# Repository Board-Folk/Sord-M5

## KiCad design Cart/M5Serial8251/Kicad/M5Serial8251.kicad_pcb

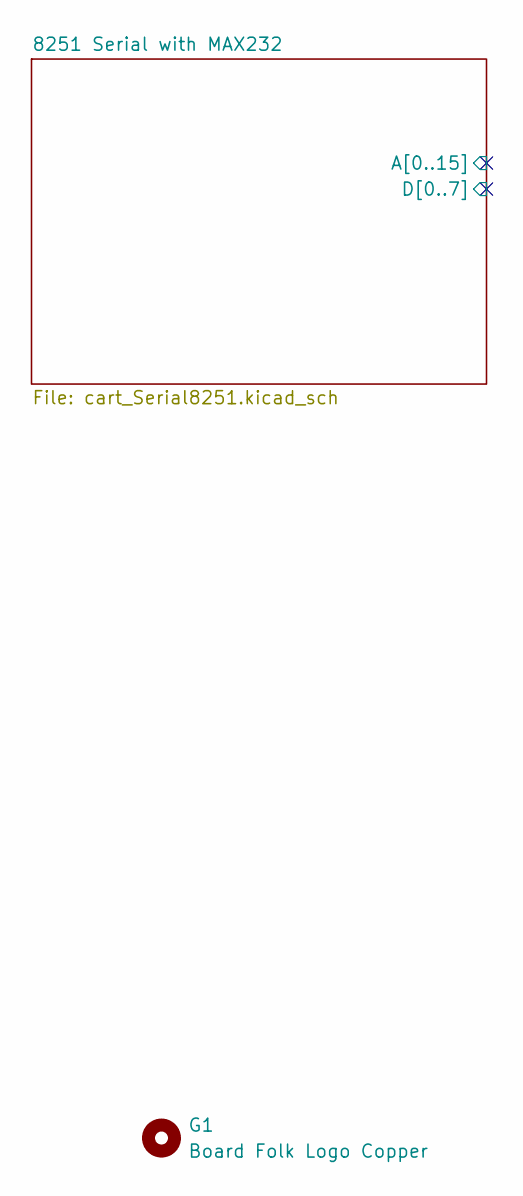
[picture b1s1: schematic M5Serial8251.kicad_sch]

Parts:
G1: Board Folk Logo Copper; BF8_copper

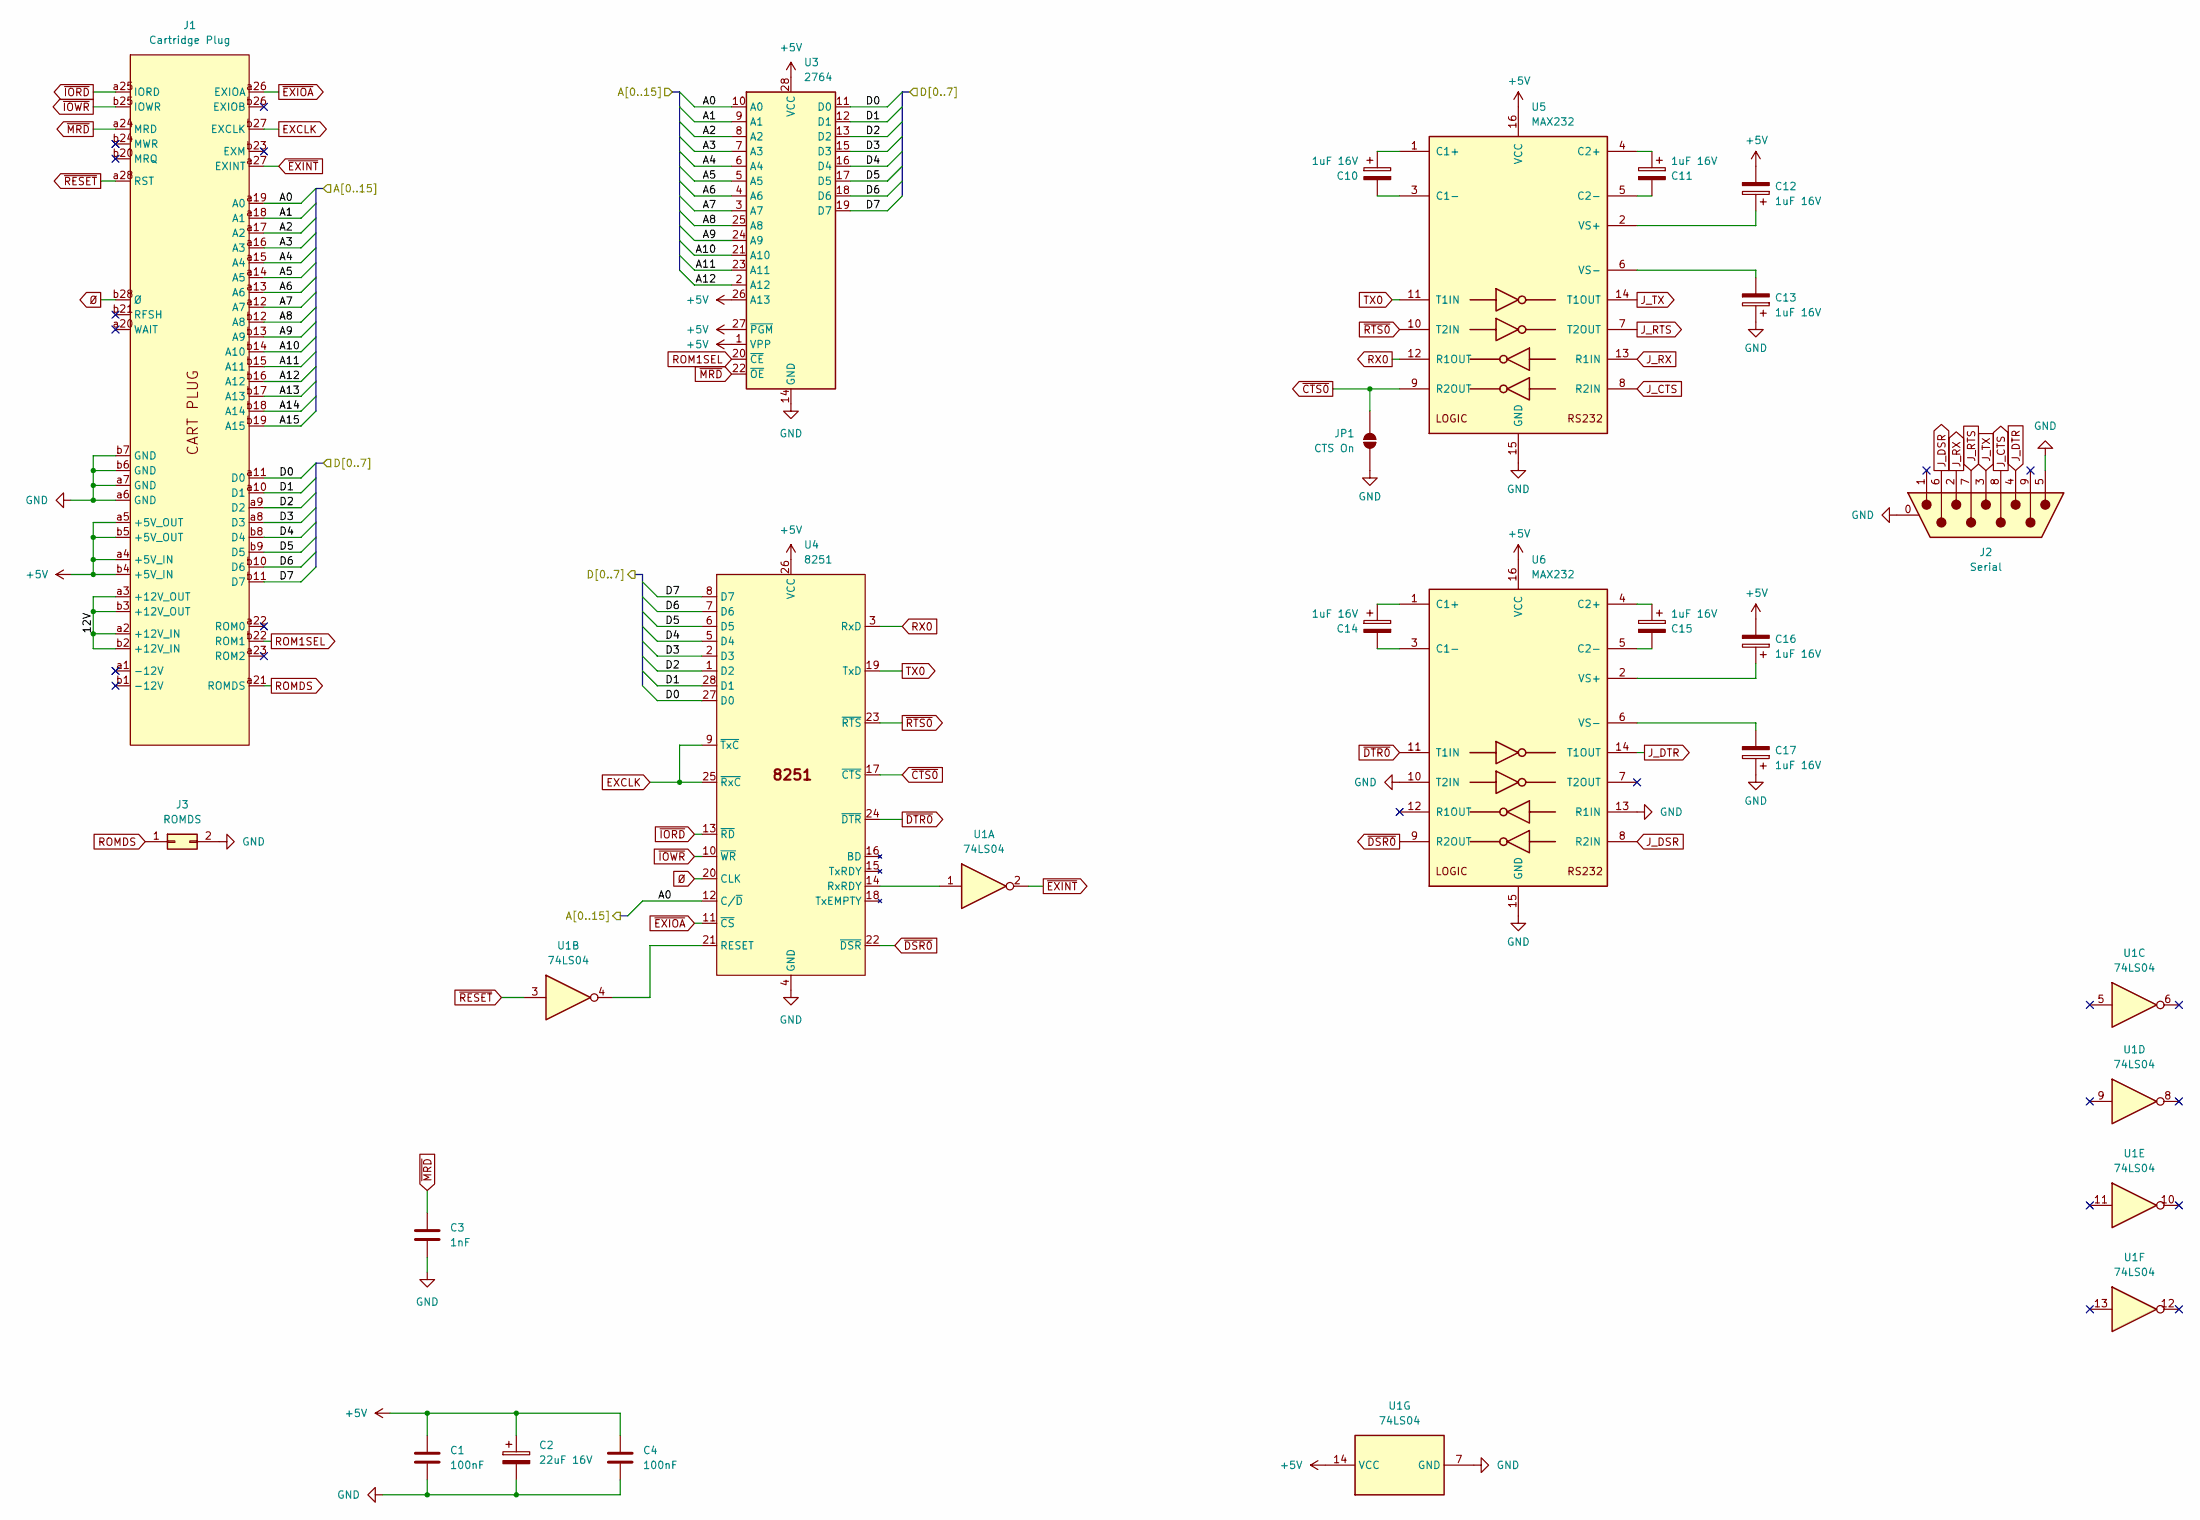
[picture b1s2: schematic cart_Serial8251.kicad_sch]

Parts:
C1, C4: 100nF; Ceramic_5mm
C2: 22uF 16V; CP_Axial_P15.00mm
C3: 1nF; Ceramic_5mm
C10, C11, C12, C13, C14, C15, C16, C17: 1uF 16V; Elect_2.54mm
J1: Cartridge Plug; Cart Edge
J2: Serial; SERIAL9
J3: ROMDS; ROM DS Select
JP1: CTS On; SolderJumper-2_P1.3mm_Open_RoundedPad1.0x1.5mm
U1: 74LS04; DIP-14_W7.62mm
U3: 2764; DIP-28_W15.24mm
U4: 8251; DIP-28_W15.24mm
U5, U6: MAX232; DIP-16_W7.62mm

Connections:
+5V: C1.1, C2.1, C4.1, C12.2, C16.2, J1.a4 (+5V_IN), J1.a5 (+5V_OUT), J1.b4 (+5V_IN), J1.b5 (+5V_OUT), U1.14 (VCC), U3.1 (VPP), U3.26 (A13), U3.27 (~PGM), U3.28 (VCC), U4.26 (VCC), U5.16 (VCC), U6.16 (VCC)
/8251 Serial with MAX232/12V: J1.a2 (+12V_IN), J1.a3 (+12V_OUT), J1.b2 (+12V_IN), J1.b3 (+12V_OUT)
/8251 Serial with MAX232/A0: J1.a19 (A0), U3.10 (A0), U4.12 (C/~D)
/8251 Serial with MAX232/A1: J1.a18 (A1), U3.9 (A1)
/8251 Serial with MAX232/A2: J1.a17 (A2), U3.8 (A2)
/8251 Serial with MAX232/A3: J1.a16 (A3), U3.7 (A3)
/8251 Serial with MAX232/A4: J1.a15 (A4), U3.6 (A4)
/8251 Serial with MAX232/A5: J1.a14 (A5), U3.5 (A5)
/8251 Serial with MAX232/A6: J1.a13 (A6), U3.4 (A6)
/8251 Serial with MAX232/A7: J1.a12 (A7), U3.3 (A7)
/8251 Serial with MAX232/A8: J1.b12 (A8), U3.25 (A8)
/8251 Serial with MAX232/A9: J1.b13 (A9), U3.24 (A9)
/8251 Serial with MAX232/A10: J1.b14 (A10), U3.21 (A10)
/8251 Serial with MAX232/A11: J1.b15 (A11), U3.23 (A11)
/8251 Serial with MAX232/A12: J1.b16 (A12), U3.2 (A12)
/8251 Serial with MAX232/A13: J1.b17 (A13)
/8251 Serial with MAX232/A14: J1.b18 (A14)
/8251 Serial with MAX232/A15: J1.b19 (A15)
/8251 Serial with MAX232/D0: J1.a11 (D0), U3.11 (D0), U4.27 (D0)
/8251 Serial with MAX232/D1: J1.a10 (D1), U3.12 (D1), U4.28 (D1)
/8251 Serial with MAX232/D2: J1.a9 (D2), U3.13 (D2), U4.1 (D2)
/8251 Serial with MAX232/D3: J1.a8 (D3), U3.15 (D3), U4.2 (D3)
/8251 Serial with MAX232/D4: J1.b8 (D4), U3.16 (D4), U4.5 (D4)
/8251 Serial with MAX232/D5: J1.b9 (D5), U3.17 (D5), U4.6 (D5)
/8251 Serial with MAX232/D6: J1.b10 (D6), U3.18 (D6), U4.7 (D6)
/8251 Serial with MAX232/D7: J1.b11 (D7), U3.19 (D7), U4.8 (D7)
EXCLK: J1.b27 (EXCLK), U4.9 (~TxC), U4.25 (~RxC)
GND: C1.2, C2.2, C3.2, C4.2, C13.1, C17.1, J1.a6 (GND), J1.a7 (GND), J1.b6 (GND), J1.b7 (GND), J2.0 (PAD), J2.5, J3.2, JP1.1 (A), U1.7 (GND), U3.14 (GND), U4.4 (GND), U5.15 (GND), U6.10 (T2IN), U6.13 (R1IN), U6.15 (GND)
J_CTS: J2.8, U5.8 (R2IN)
J_DSR: J2.6, U6.8 (R2IN)
J_DTR: J2.4, U6.14 (T1OUT)
J_RTS: J2.7, U5.7 (T2OUT)
J_RX: J2.2, U5.13 (R1IN)
J_TX: J2.3, U5.14 (T1OUT)
unnamed: U1.4, U4.21 (RESET)
unnamed: U1.1, U4.14 (RxRDY)
unnamed: C10.1, U5.1 (C1+)
unnamed: C10.2, U5.3 (C1-)
unnamed: C11.1, U5.4 (C2+)
unnamed: C11.2, U5.5 (C2-)
unnamed: C12.1, U5.2 (VS+)
unnamed: C13.2, U5.6 (VS-)
unnamed: C14.1, U6.1 (C1+)
unnamed: C14.2, U6.3 (C1-)
unnamed: C15.1, U6.4 (C2+)
unnamed: C15.2, U6.5 (C2-)
unnamed: C16.1, U6.2 (VS+)
unnamed: C17.2, U6.6 (VS-)
ROM1SEL: J1.b22 (ROM1), U3.20 (~CE)
ROMDS: J1.a21 (ROMDS), J3.1
RX0: U4.3 (RxD), U5.12 (R1OUT)
TX0: U4.19 (TxD), U5.11 (T1IN)
~CTS0: JP1.2 (B), U4.17 (~CTS), U5.9 (R2OUT)
~DSR0: U4.22 (~DSR), U6.9 (R2OUT)
~DTR0: U4.24 (~DTR), U6.11 (T1IN)
~EXINT: J1.a27 (EXINT), U1.2
~EXIOA: J1.a26 (EXIOA), U4.11 (~CS)
~IORD: J1.a25 (IORD), U4.13 (~RD)
~IOWR: J1.b25 (IOWR), U4.10 (~WR)
~MRD: C3.1, J1.a24 (MRD), U3.22 (~OE)
~RESET: J1.a28 (RST), U1.3
~RTS0: U4.23 (~RTS), U5.10 (T2IN)
Ø: J1.b28 (Ø), U4.20 (CLK)

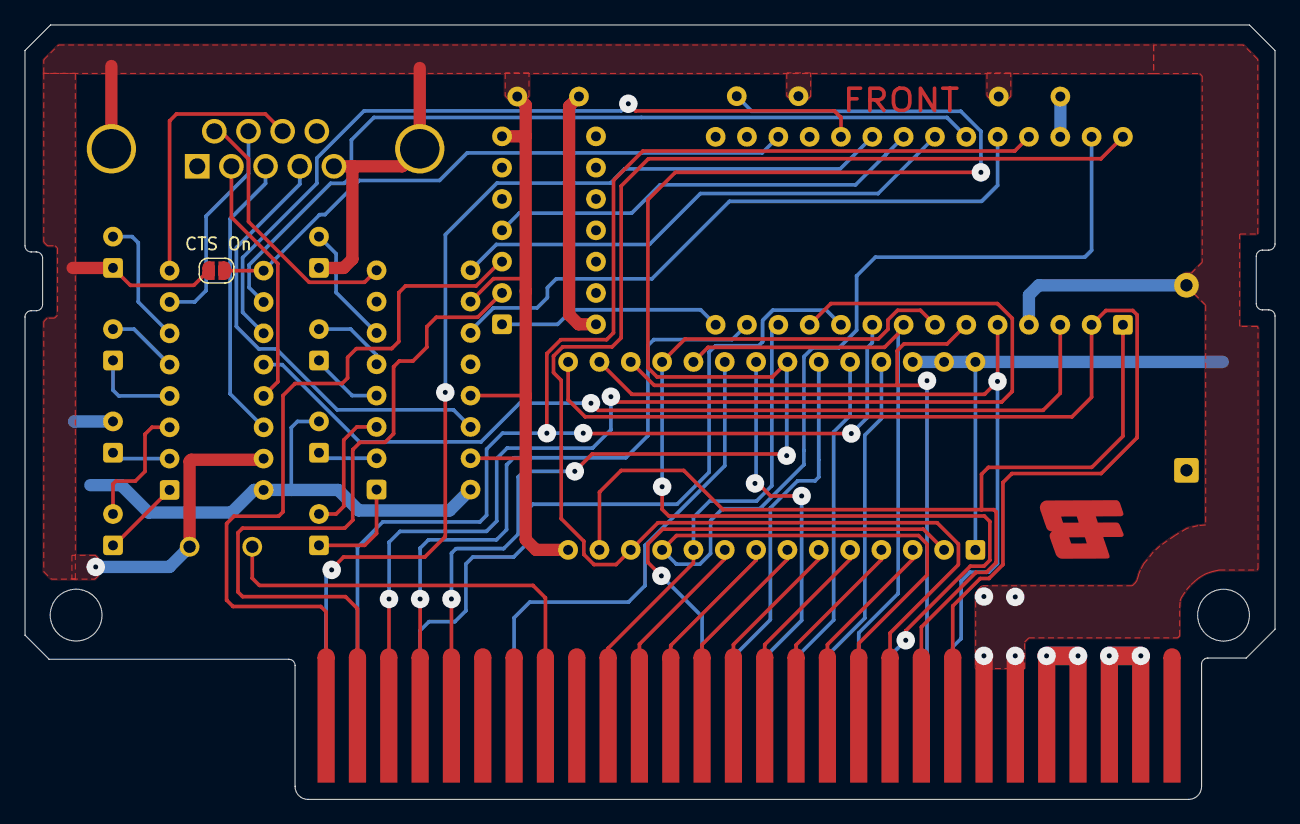
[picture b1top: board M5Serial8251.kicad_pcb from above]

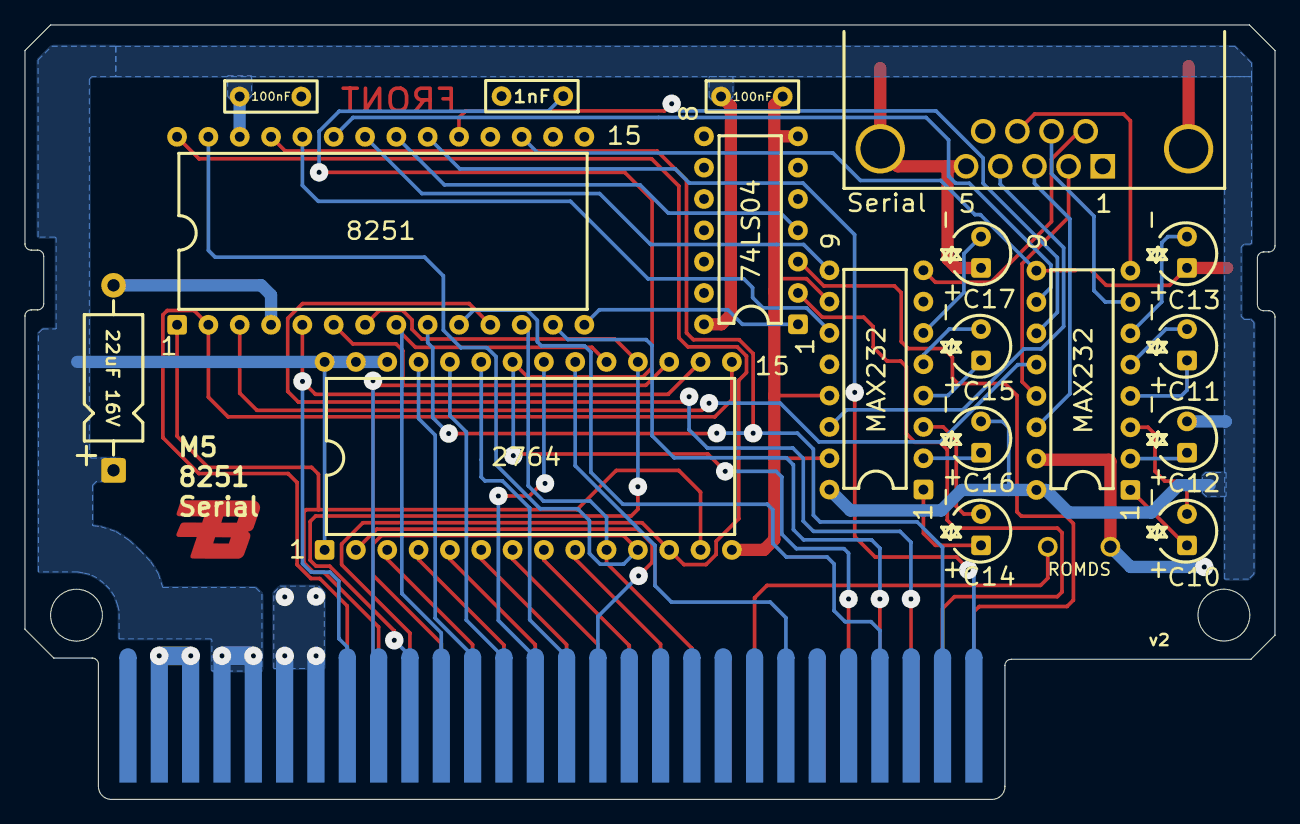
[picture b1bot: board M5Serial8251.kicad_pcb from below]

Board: 2 copper layers, 101.3 x 62.8 mm, 22 parts (19 on the bottom side), 60 nets.

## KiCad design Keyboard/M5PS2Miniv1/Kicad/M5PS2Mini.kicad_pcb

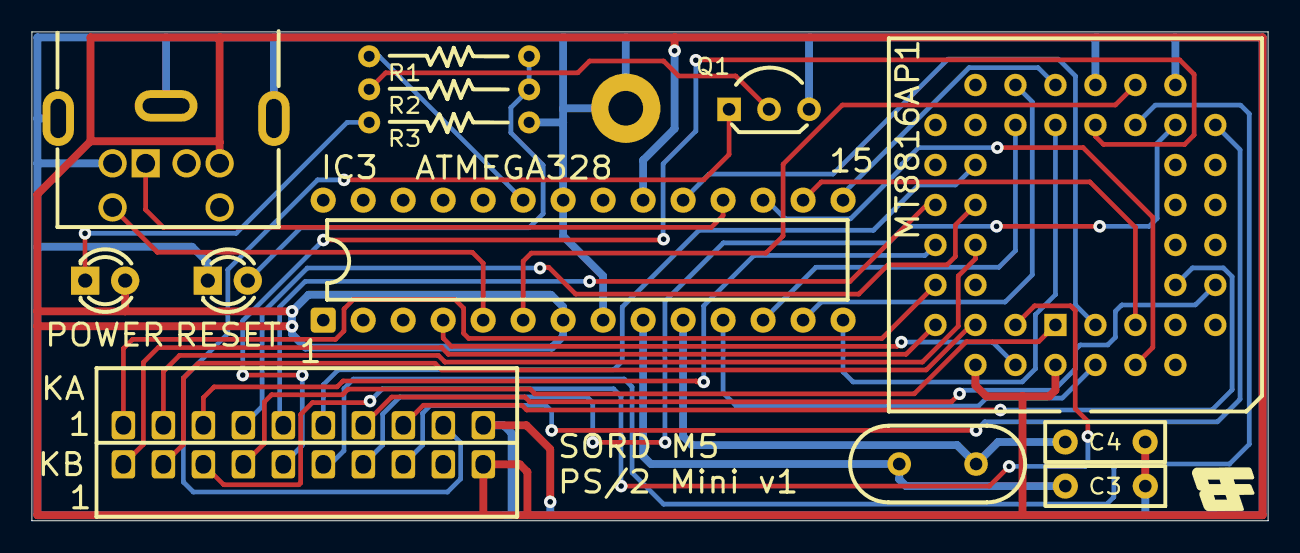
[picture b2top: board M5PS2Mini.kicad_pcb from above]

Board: 2 copper layers, 78.5 x 31.1 mm, 16 parts (0 on the bottom side), 37 nets.

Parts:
C3, C4: 20pF; Ceramic_5.08mm
CN7: GND Pad; MountingHole_2.2mm_M2_Pad
D1: POWER; LED_D3.0mm
D2: RESET; LED_D3.0mm
G1: Board Folk Logo; bf4
IC3: ATMEGA328; DIP-28_W7.62mm
IC4: MT8816AP1; PLCC-44_THT-Socket
J2: PS/2; Connector_Mini-DIN_Female_6Pin_2rows
KA1: KA; PinSocket_1x10
KB1: KB; PinSocket_1x10
Q1: BC517; TO-92_Standard
R1: 470R; R_Axial_10.16mm
R2, R3: 1K; R_Axial_10.16mm
Y1: 16MHz; Crystal_Vertical

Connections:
+5V: D1.2 (A), IC3.7 (VCC), IC3.20 (AVCC), IC4.40 (CS), IC4.44 (VDD), J2.4, KB1.10
AX0: IC3.16 (PB2), IC4.5 (AX0)
AX1: IC3.15 (PB1), IC4.24 (AX1)
AX2: IC3.14 (PB0), IC4.25 (AX2)
AX3: IC3.17 (PB3), IC4.4 (AX3)
AY0: IC3.13 (PD7), IC4.26 (AY0)
AY1: IC3.12 (PD6), IC4.27 (AY1)
AY2: IC3.11 (PD5), IC4.2 (AY2)
BREAK: IC3.23 (PC0), R1.1
GND: C3.1, C4.1, CN7.1 (1_1), D2.1 (K), IC3.8 (GND), IC3.22 (GND), IC4.18 (VSS), IC4.22 (VEE), J2.3, J2.7 (GND_7), KA1.10, Q1.3 (E), R3.2
MTDATA: IC3.4 (PD2), IC4.42 (DATA)
MTRESET: IC3.19 (PB5), IC4.3 (RESET)
MTSTROBE: IC3.6 (PD4), IC4.20 (STROBE)
unnamed: D1.1 (K), R3.1
unnamed: D2.2 (A), R1.2, R2.2
unnamed: C3.2, IC3.9 (PB6), Y1.1
unnamed: C4.2, IC3.10 (PB7), Y1.2
unnamed: Q1.2 (B), R2.1
PS2-CLK: IC3.5 (PD3), J2.5
PS2-DATA: IC3.18 (PB4), J2.1
RSTK: KA1.9, Q1.1 (C)
X0: IC4.37 (X0), KA1.1
X1: IC4.36 (X1), KA1.2
X2: IC4.35 (X2), KA1.3
X3: IC4.34 (X3), KA1.4
X4: IC4.33 (X4), KA1.5
X5: IC4.32 (X5), KA1.6
X6: IC4.9 (X6), KA1.7
X7: IC4.10 (X7), KA1.8
Y0: IC4.39 (Y0), KB1.1
Y1: IC4.41 (Y1), KB1.2
Y2: IC4.43 (Y2), KB1.3
Y3: IC4.1 (Y3), KB1.4
Y4: IC4.23 (Y4), KB1.5
Y5: IC4.21 (Y5), KB1.6
Y6: IC4.19 (Y6), KB1.7
Y7: IC4.17 (Y7), KB1.8

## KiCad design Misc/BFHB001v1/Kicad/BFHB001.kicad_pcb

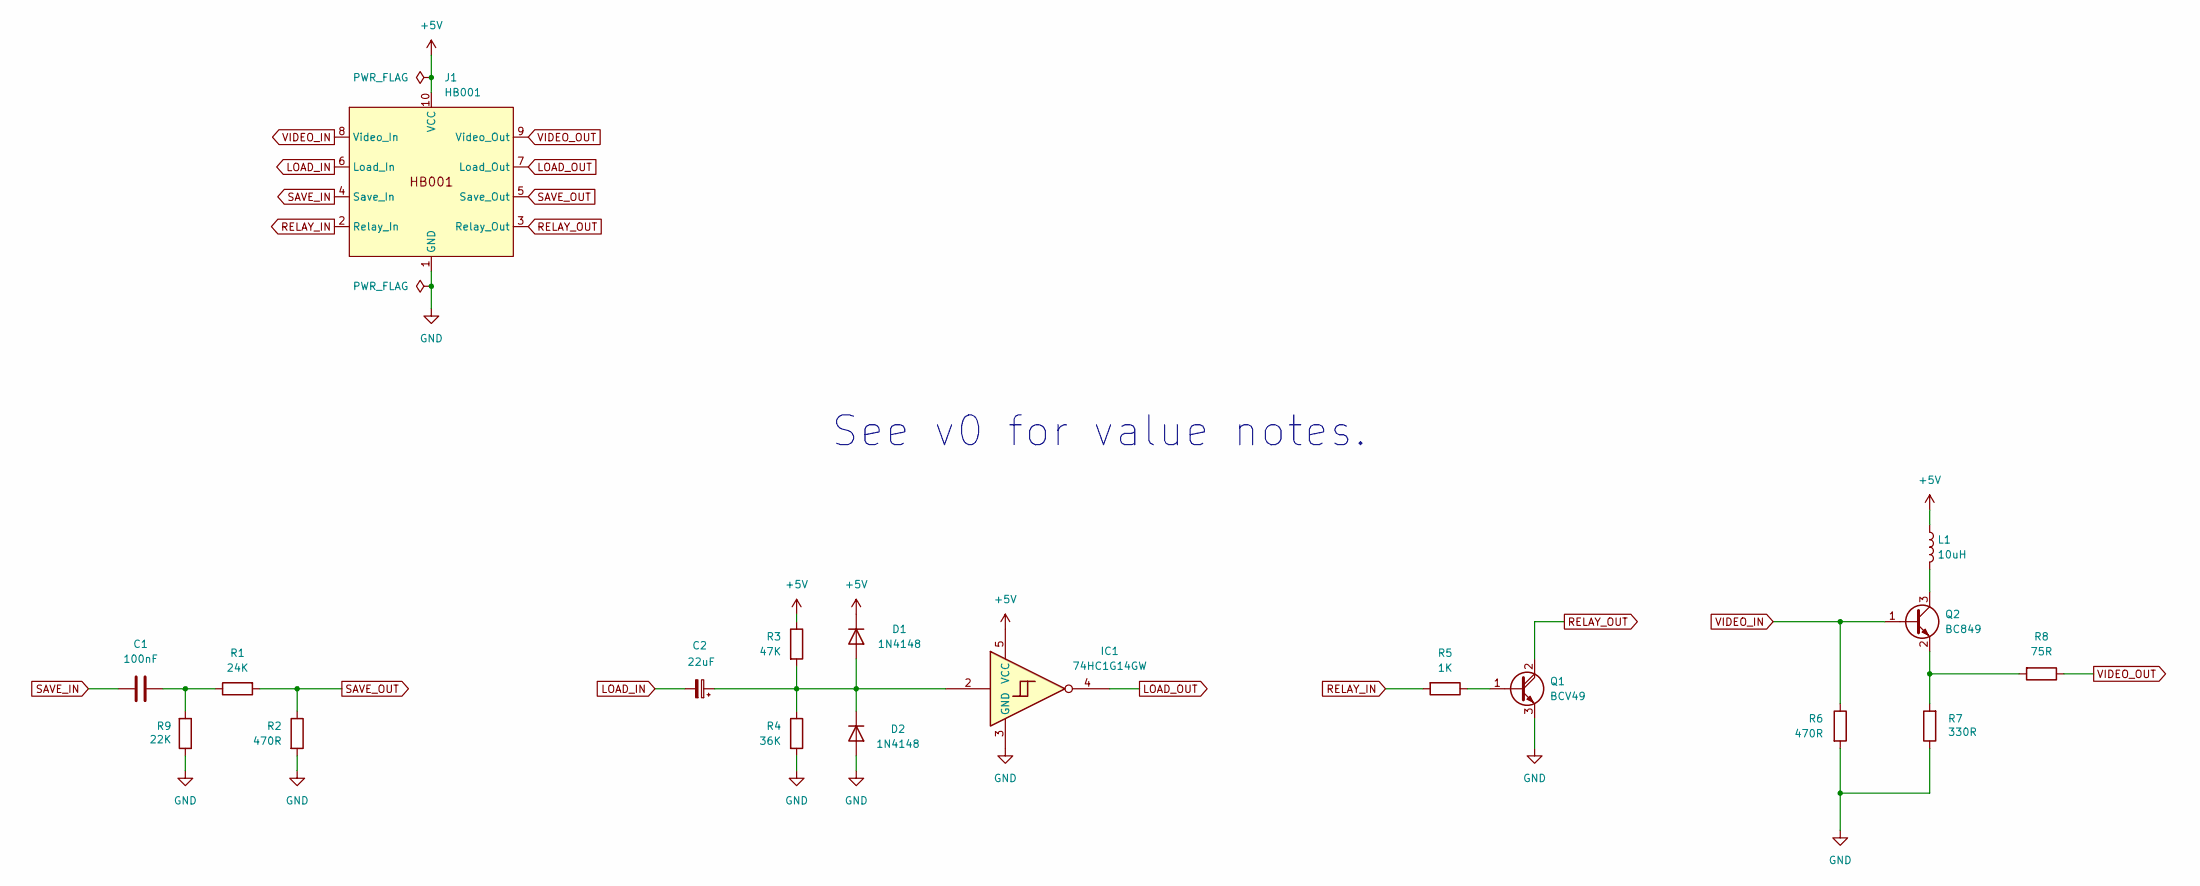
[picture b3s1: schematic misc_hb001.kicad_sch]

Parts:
C1: 100nF; C_0805_2012Metric
C2: 22uF; CP_Elec_5x5.4
D1, D2: 1N4148; D_SOD-123
IC1: 74HC1G14GW; SOT-353_SC-70-5
J1: HB001; SIP10_EDGE
L1: 10uH; L_0805_2012Metric
Q1: BCV49; SOT-89-3
Q2: BC849; SOT-23
R1: 24K; R_0805_2012Metric
R2, R6: 470R; R_0805_2012Metric
R3: 47K; R_0805_2012Metric
R4: 36K; R_0805_2012Metric
R5: 1K; R_0805_2012Metric
R7: 330R; R_0805_2012Metric
R8: 75R; R_0805_2012Metric
R9: 22K; R_0805_2012Metric

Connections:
+5V: D1.1 (K), IC1.5 (VCC), J1.10 (VCC), L1.1, R3.1
GND: D2.2 (A), IC1.3 (GND), J1.1 (GND), Q1.3 (E), R2.2, R4.2, R6.2, R7.1, R9.1
LOAD_IN: C2.2, J1.6 (Load_In)
LOAD_OUT: IC1.4, J1.7 (Load_Out)
unnamed: C1.2, R1.1, R9.2
unnamed: C2.1, D1.2 (A), D2.1 (K), IC1.2, R3.2, R4.1
unnamed: Q1.1 (B), R5.1
unnamed: L1.2, Q2.3 (C)
unnamed: Q2.2 (E), R7.2, R8.2
RELAY_IN: J1.2 (Relay_In), R5.2
RELAY_OUT: J1.3 (Relay_Out), Q1.2 (C)
SAVE_IN: C1.1, J1.4 (Save_In)
SAVE_OUT: J1.5 (Save_Out), R1.2, R2.1
VIDEO_IN: J1.8 (Video_In), Q2.1 (B), R6.1
VIDEO_OUT: J1.9 (Video_Out), R8.1

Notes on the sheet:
See v0 for value notes.

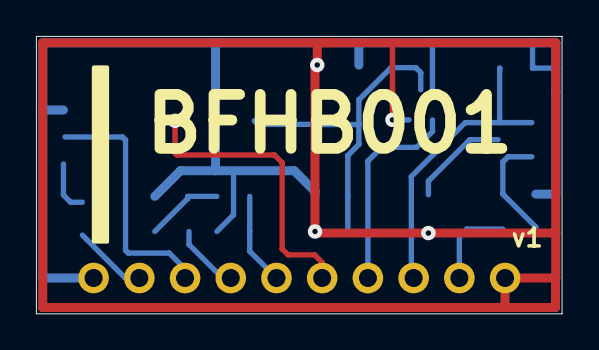
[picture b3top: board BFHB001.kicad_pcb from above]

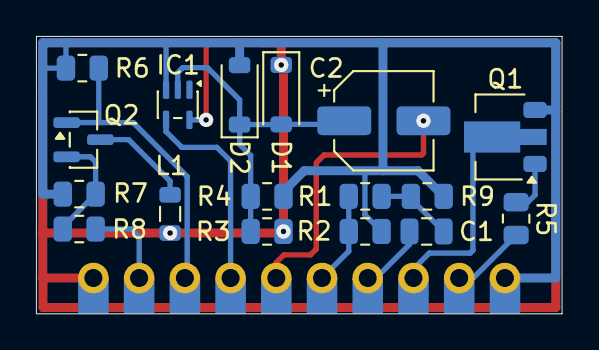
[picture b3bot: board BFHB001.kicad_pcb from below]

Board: 2 copper layers, 29.2 x 15.4 mm, 18 parts (17 on the bottom side), 15 nets.
